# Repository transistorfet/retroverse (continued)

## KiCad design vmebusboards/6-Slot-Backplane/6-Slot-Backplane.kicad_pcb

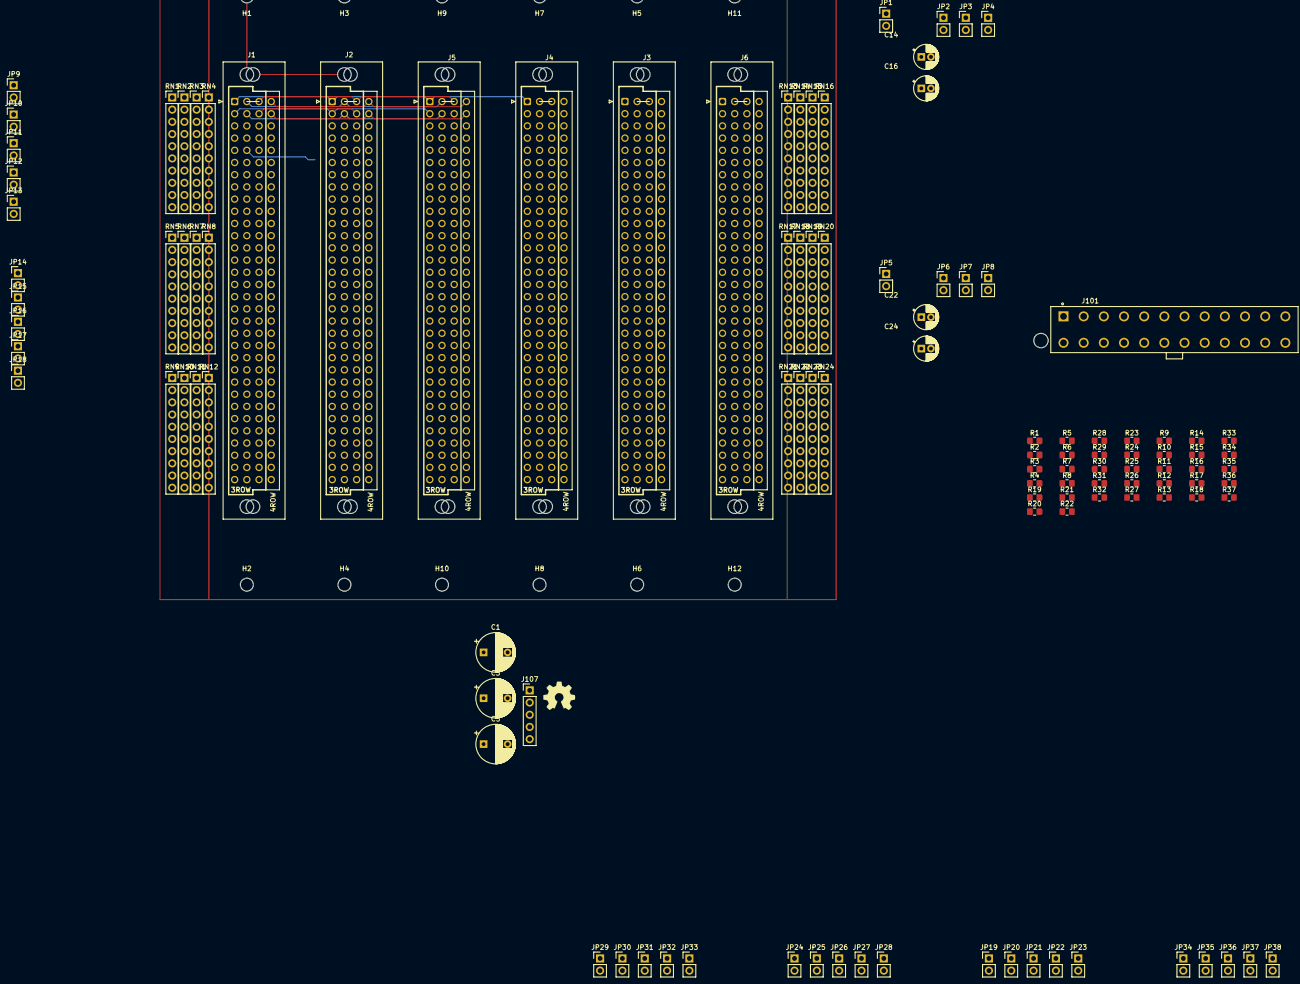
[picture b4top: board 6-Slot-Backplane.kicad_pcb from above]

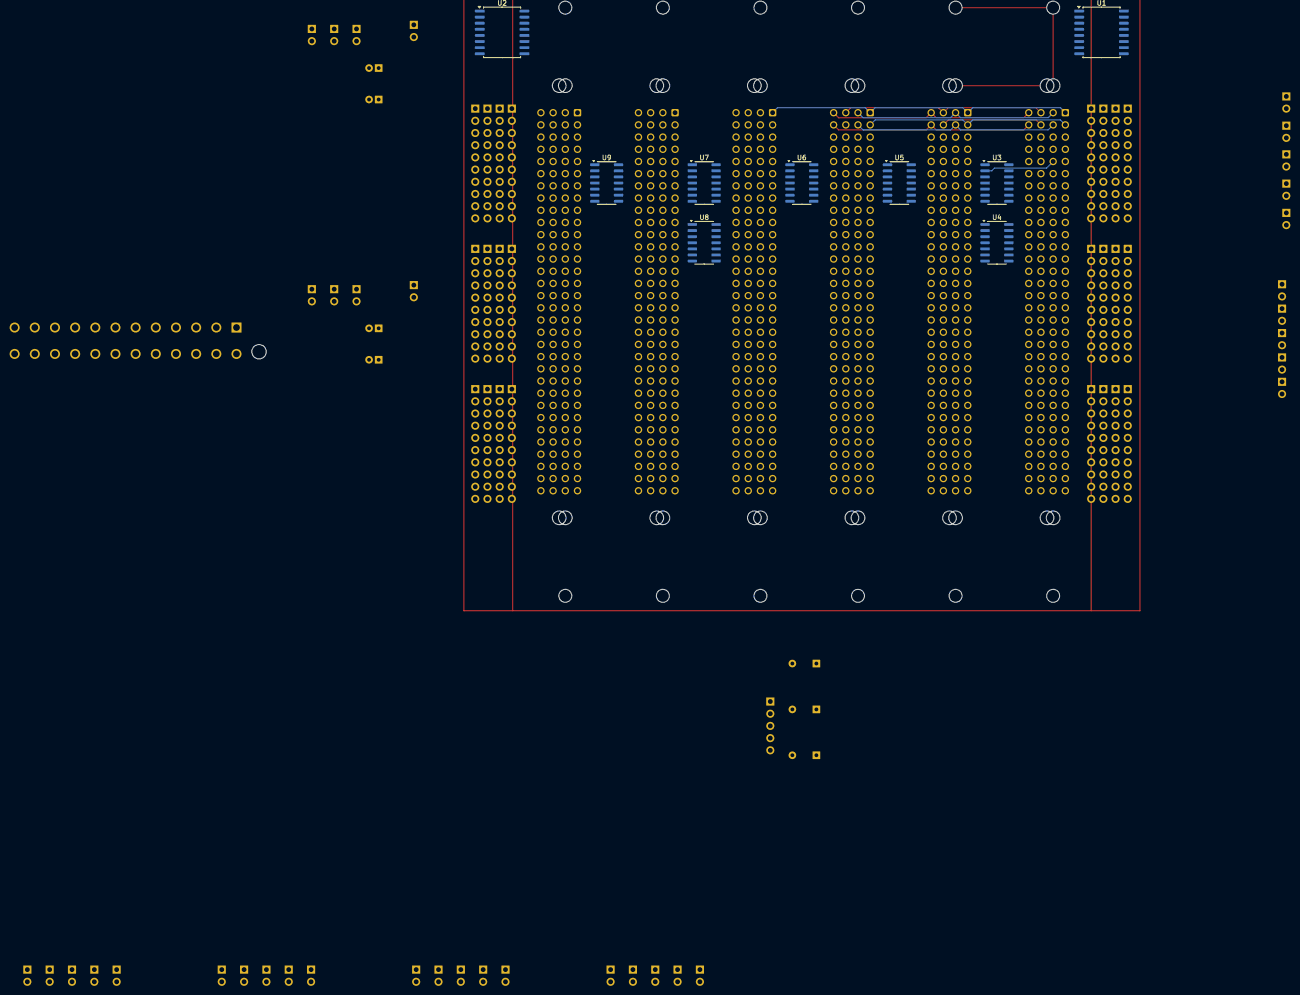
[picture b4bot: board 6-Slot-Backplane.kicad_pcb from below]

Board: 4 copper layers, 136 parts (9 on the bottom side), 139 nets.

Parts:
C1, C3, C5: 10uF; CP_Radial_D8.0mm_P5.00mm
C14, C16, C22, C24: 4.7uF; CP_Radial_D5.0mm_P2.00mm
H1, H2, H3, H4, H5, H6, H7, H8, H9, H10, H11, H12: MountingHole; MountingHole_2.7mm_M2.5_DIN965
J1, J2, J3, J4, J5, J6: VME-J1-4R-NS; DIN41612_C_4x32_Female_Vertical_THT
J101: ATX-24; TE_1-1775099-3_ATX_24_Pin_PowerSupply
J107: SYSTEM MONITOR; PinHeader_1x05_P2.54mm_Vertical
JP1, JP2, JP3, JP4, JP5, JP6, JP7, JP8: PASSIVE/ACTIVE; PinHeader_1x02_P2.54mm_Vertical
JP9: BR0 LOOPBACK; PinHeader_1x02_P2.54mm_Vertical
JP10: BR1 LOOPBACK; PinHeader_1x02_P2.54mm_Vertical
JP11: BR2 LOOPBACK; PinHeader_1x02_P2.54mm_Vertical
JP12: BR3 LOOPBACK; PinHeader_1x02_P2.54mm_Vertical
JP13: IACK LOOPBACK; PinHeader_1x02_P2.54mm_Vertical
JP14, JP19, JP24, JP29, JP34: BG0; PinHeader_1x02_P2.54mm_Vertical
JP15, JP20, JP25, JP30, JP35: BG1; PinHeader_1x02_P2.54mm_Vertical
JP16, JP21, JP26, JP31, JP36: BG2; PinHeader_1x02_P2.54mm_Vertical
JP17, JP22, JP27, JP32, JP37: BG3; PinHeader_1x02_P2.54mm_Vertical
JP18, JP23, JP28, JP33, JP38: IACK; PinHeader_1x02_P2.54mm_Vertical
R1, R4, R6, R8, R20, R22: 470; R_0805_2012Metric_Pad1.20x1.40mm_HandSolder
R2, R3, R5, R7, R19, R21: 330; R_0805_2012Metric_Pad1.20x1.40mm_HandSolder
R9, R10, R11, R12, R13, R14, R15, R16, R17, R18, R23, R24, R25, R26, R27, R28, R29, R30, R31, R32, R33, R34, R35, R36, R37: 82k; R_0805_2012Metric_Pad1.20x1.40mm_HandSolder
RN1, RN2, RN3, RN4, RN5, RN6, RN7, RN8, RN9, RN10, RN11, RN12, RN13, RN14, RN15, RN16, RN17, RN18, RN19, RN20, RN21, RN22, RN23, RN24: 4610X-104-331/471L; PinHeader_1x10_P2.54mm_Vertical
S1: Logo_Open_Hardware_Small; OSHW-Symbol_6.7x6mm_SilkScreen
U1, U2: TCA0372_Dual_OpAmp; SOIC-16W_7.5x10.3mm_P1.27mm
U3, U4, U5, U6, U7, U8, U9: 74ACT32; SOIC-14_3.9x8.7mm_P1.27mm

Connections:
+5V: C1.1, J1.a32 (+5V), J1.b32 (+5V), J1.c32 (+5V), J1.d1 (+5V), J1.d13 (+5V), J1.d32 (+5V), J2.a32 (+5V), J2.b32 (+5V), J2.c32 (+5V), J2.d1 (+5V), J2.d13 (+5V), J2.d32 (+5V), J3.a32 (+5V), J3.b32 (+5V), J3.c32 (+5V), J3.d1 (+5V), J3.d13 (+5V), J3.d32 (+5V), J4.a32 (+5V), J4.b32 (+5V), J4.c32 (+5V), J4.d1 (+5V), J4.d13 (+5V), J4.d32 (+5V), J5.a32 (+5V), J5.b32 (+5V), J5.c32 (+5V), J5.d1 (+5V), J5.d13 (+5V), J5.d32 (+5V), J6.a32 (+5V), J6.b32 (+5V), J6.c32 (+5V), J6.d1 (+5V), J6.d13 (+5V), J6.d32 (+5V), J101.4 (+5V), J101.6 (+5V), J101.21 (+5V), J101.22 (+5V), J101.23 (+5V), J107.4, JP1.1 (A), JP3.1 (A), JP5.1 (A), JP7.1 (A), R3.1, R7.1, R19.1, R21.1, U1.1 (V+), U2.1 (V+), U3.14 (VCC), U4.14 (VCC), U5.14 (VCC), U6.14 (VCC), U7.14 (VCC), U8.14 (VCC), U9.14 (VCC)
+5VStdby: J1.b31 (+5VStdby), J2.b31 (+5VStdby), J3.b31 (+5VStdby), J4.b31 (+5VStdby), J5.b31 (+5VStdby), J6.b31 (+5VStdby), J101.9 (+5VSB)
+12V: C3.1, J1.c31 (+12V), J2.c31 (+12V), J3.c31 (+12V), J4.c31 (+12V), J5.c31 (+12V), J6.c31 (+12V), J101.10 (+12V), J101.11 (+12V)
-12V: C5.1, J1.a31 (-12V), J2.a31 (-12V), J3.a31 (-12V), J4.a31 (-12V), J5.a31 (-12V), J6.a31 (-12V), J101.14 (-12V)
A1: J1.a30 (A01), J2.a30 (A01), J3.a30 (A01), J4.a30 (A01), J5.a30 (A01), J6.a30 (A01), RN3.2 (R1), RN23.2 (R1)
A2: J1.a29 (A02), J2.a29 (A02), J3.a29 (A02), J4.a29 (A02), J5.a29 (A02), J6.a29 (A02), RN3.3 (R2), RN23.3 (R2)
A3: J1.a28 (A03), J2.a28 (A03), J3.a28 (A03), J4.a28 (A03), J5.a28 (A03), J6.a28 (A03), RN3.4 (R3), RN23.4 (R3)
A4: J1.a27 (A04), J2.a27 (A04), J3.a27 (A04), J4.a27 (A04), J5.a27 (A04), J6.a27 (A04), RN3.5 (R4), RN23.5 (R4)
A5: J1.a26 (A05), J2.a26 (A05), J3.a26 (A05), J4.a26 (A05), J5.a26 (A05), J6.a26 (A05), RN3.6 (R5), RN23.6 (R5)
A6: J1.a25 (A06), J2.a25 (A06), J3.a25 (A06), J4.a25 (A06), J5.a25 (A06), J6.a25 (A06), RN3.7 (R6), RN23.7 (R6)
A7: J1.a24 (A07), J2.a24 (A07), J3.a24 (A07), J4.a24 (A07), J5.a24 (A07), J6.a24 (A07), RN3.8 (R7), RN23.8 (R7)
A8: J1.c30 (A8), J2.c30 (A8), J3.c30 (A8), J4.c30 (A8), J5.c30 (A8), J6.c30 (A8), RN4.2 (R1), RN24.2 (R1)
A9: J1.c29 (A9), J2.c29 (A9), J3.c29 (A9), J4.c29 (A9), J5.c29 (A9), J6.c29 (A9), RN4.3 (R2), RN24.3 (R2)
A10: J1.c28 (A10), J2.c28 (A10), J3.c28 (A10), J4.c28 (A10), J5.c28 (A10), J6.c28 (A10), RN4.4 (R3), RN24.4 (R3)
A11: J1.c27 (A11), J2.c27 (A11), J3.c27 (A11), J4.c27 (A11), J5.c27 (A11), J6.c27 (A11), RN4.5 (R4), RN24.5 (R4)
A12: J1.c26 (A12), J2.c26 (A12), J3.c26 (A12), J4.c26 (A12), J5.c26 (A12), J6.c26 (A12), RN4.6 (R5), RN24.6 (R5)
A13: J1.c25 (A13), J2.c25 (A13), J3.c25 (A13), J4.c25 (A13), J5.c25 (A13), J6.c25 (A13), RN4.7 (R6), RN24.7 (R6)
A14: J1.c24 (A14), J2.c24 (A14), J3.c24 (A14), J4.c24 (A14), J5.c24 (A14), J6.c24 (A14), RN4.8 (R7), RN24.8 (R7)
A15: J1.c23 (A15), J2.c23 (A15), J3.c23 (A15), J4.c23 (A15), J5.c23 (A15), J6.c23 (A15), RN4.9 (R8), RN24.9 (R8)
A16: J1.c22 (A16), J2.c22 (A16), J3.c22 (A16), J4.c22 (A16), J5.c22 (A16), J6.c22 (A16), RN5.2 (R1), RN17.2 (R1)
A17: J1.c21 (A17), J2.c21 (A17), J3.c21 (A17), J4.c21 (A17), J5.c21 (A17), J6.c21 (A17), RN5.3 (R2), RN17.3 (R2)
A18: J1.c20 (A18), J2.c20 (A18), J3.c20 (A18), J4.c20 (A18), J5.c20 (A18), J6.c20 (A18), RN5.4 (R3), RN17.4 (R3)
A19: J1.c19 (A19), J2.c19 (A19), J3.c19 (A19), J4.c19 (A19), J5.c19 (A19), J6.c19 (A19), RN5.5 (R4), RN17.5 (R4)
A20: J1.c18 (A20), J2.c18 (A20), J3.c18 (A20), J4.c18 (A20), J5.c18 (A20), J6.c18 (A20), RN5.6 (R5), RN17.6 (R5)
A21: J1.c17 (A21), J2.c17 (A21), J3.c17 (A21), J4.c17 (A21), J5.c17 (A21), J6.c17 (A21), RN5.7 (R6), RN17.7 (R6)
A22: J1.c16 (A22), J2.c16 (A22), J3.c16 (A22), J4.c16 (A22), J5.c16 (A22), J6.c16 (A22), RN5.8 (R7), RN17.8 (R7)
A23: J1.c15 (A23), J2.c15 (A23), J3.c15 (A23), J4.c15 (A23), J5.c15 (A23), J6.c15 (A23), RN5.9 (R8), RN17.9 (R8)
A24: J1.d4 (A24), J2.d4 (A24), J3.d4 (A24), J4.d4 (A24), J5.d4 (A24), J6.d4 (A24), RN6.2 (R1), RN18.2 (R1)
A25: J1.d5 (A25), J2.d5 (A25), J3.d5 (A25), J4.d5 (A25), J5.d5 (A25), J6.d5 (A25), RN6.3 (R2), RN18.3 (R2)
A26: J1.d6 (A26), J2.d6 (A26), J3.d6 (A26), J4.d6 (A26), J5.d6 (A26), J6.d6 (A26), RN6.4 (R3), RN18.4 (R3)
A27: J1.d7 (A27), J2.d7 (A27), J3.d7 (A27), J4.d7 (A27), J5.d7 (A27), J6.d7 (A27), RN6.5 (R4), RN18.5 (R4)
A28: J1.d8 (A28), J2.d8 (A28), J3.d8 (A28), J4.d8 (A28), J5.d8 (A28), J6.d8 (A28), RN6.6 (R5), RN18.6 (R5)
A29: J1.d9 (A29), J2.d9 (A29), J3.d9 (A29), J4.d9 (A29), J5.d9 (A29), J6.d9 (A29), RN6.7 (R6), RN18.7 (R6)
A30: J1.d10 (A30), J2.d10 (A30), J3.d10 (A30), J4.d10 (A30), J5.d10 (A30), J6.d10 (A30), RN6.8 (R7), RN18.8 (R7)
A31: J1.d11 (A31), J2.d11 (A31), J3.d11 (A31), J4.d11 (A31), J5.d11 (A31), J6.d11 (A31), RN6.9 (R8), RN18.9 (R8)
AM0: J1.b16 (AM0), J2.b16 (AM0), J3.b16 (AM0), J4.b16 (AM0), J5.b16 (AM0), J6.b16 (AM0), RN10.9 (R8), RN14.9 (R8)
AM1: J1.b17 (AM1), J2.b17 (AM1), J3.b17 (AM1), J4.b17 (AM1), J5.b17 (AM1), J6.b17 (AM1), RN11.2 (R1), RN15.2 (R1)
AM2: J1.b18 (AM2), J2.b18 (AM2), J3.b18 (AM2), J4.b18 (AM2), J5.b18 (AM2), J6.b18 (AM2), RN11.3 (R2), RN15.3 (R2)
AM3: J1.b19 (AM3), J2.b19 (AM3), J3.b19 (AM3), J4.b19 (AM3), J5.b19 (AM3), J6.b19 (AM3), RN11.4 (R3), RN15.4 (R3)
AM4: J1.a23 (AM4), J2.a23 (AM4), J3.a23 (AM4), J4.a23 (AM4), J5.a23 (AM4), J6.a23 (AM4), RN9.9 (R8), RN13.9 (R8)
AM5: J1.c14 (AM5), J2.c14 (AM5), J3.c14 (AM5), J4.c14 (AM5), J5.c14 (AM5), J6.c14 (AM5), RN3.9 (R8), RN23.9 (R8)
D0: J1.a1 (D00), J2.a1 (D00), J3.a1 (D00), J4.a1 (D00), J5.a1 (D00), J6.a1 (D00), RN1.2 (R1), RN21.2 (R1)
D1: J1.a2 (D01), J2.a2 (D01), J3.a2 (D01), J4.a2 (D01), J5.a2 (D01), J6.a2 (D01), RN1.3 (R2), RN21.3 (R2)
D2: J1.a3 (D02), J2.a3 (D02), J3.a3 (D02), J4.a3 (D02), J5.a3 (D02), J6.a3 (D02), RN1.4 (R3), RN21.4 (R3)
D3: J1.a4 (D03), J2.a4 (D03), J3.a4 (D03), J4.a4 (D03), J5.a4 (D03), J6.a4 (D03), RN1.5 (R4), RN21.5 (R4)
D4: J1.a5 (D04), J2.a5 (D04), J3.a5 (D04), J4.a5 (D04), J5.a5 (D04), J6.a5 (D04), RN1.6 (R5), RN21.6 (R5)
D5: J1.a6 (D05), J2.a6 (D05), J3.a6 (D05), J4.a6 (D05), J5.a6 (D05), J6.a6 (D05), RN1.7 (R6), RN21.7 (R6)
D6: J1.a7 (D06), J2.a7 (D06), J3.a7 (D06), J4.a7 (D06), J5.a7 (D06), J6.a7 (D06), RN1.8 (R7), RN21.8 (R7)
D7: J1.a8 (D07), J2.a8 (D07), J3.a8 (D07), J4.a8 (D07), J5.a8 (D07), J6.a8 (D07), RN1.9 (R8), RN21.9 (R8)
D8: J1.c1 (D08), J2.c1 (D08), J3.c1 (D08), J4.c1 (D08), J5.c1 (D08), J6.c1 (D08), RN2.2 (R1), RN22.2 (R1)
D9: J1.c2 (D09), J2.c2 (D09), J3.c2 (D09), J4.c2 (D09), J5.c2 (D09), J6.c2 (D09), RN2.3 (R2), RN22.3 (R2)
D10: J1.c3 (D10), J2.c3 (D10), J3.c3 (D10), J4.c3 (D10), J5.c3 (D10), J6.c3 (D10), RN2.4 (R3), RN22.4 (R3)
D11: J1.c4 (D11), J2.c4 (D11), J3.c4 (D11), J4.c4 (D11), J5.c4 (D11), J6.c4 (D11), RN2.5 (R4), RN22.5 (R4)
D12: J1.c5 (D12), J2.c5 (D12), J3.c5 (D12), J4.c5 (D12), J5.c5 (D12), J6.c5 (D12), RN2.6 (R5), RN22.6 (R5)
D13: J1.c6 (D13), J2.c6 (D13), J3.c6 (D13), J4.c6 (D13), J5.c6 (D13), J6.c6 (D13), RN2.7 (R6), RN22.7 (R6)
D14: J1.c7 (D14), J2.c7 (D14), J3.c7 (D14), J4.c7 (D14), J5.c7 (D14), J6.c7 (D14), RN2.8 (R7), RN22.8 (R7)
D15: J1.c8 (D15), J2.c8 (D15), J3.c8 (D15), J4.c8 (D15), J5.c8 (D15), J6.c8 (D15), RN2.9 (R8), RN22.9 (R8)
D16: J1.d14 (D16), J2.d14 (D16), J3.d14 (D16), J4.d14 (D16), J5.d14 (D16), J6.d14 (D16), RN7.2 (R1), RN19.2 (R1)
D17: J1.d15 (D17), J2.d15 (D17), J3.d15 (D17), J4.d15 (D17), J5.d15 (D17), J6.d15 (D17), RN7.3 (R2), RN19.3 (R2)
D18: J1.d16 (D18), J2.d16 (D18), J3.d16 (D18), J4.d16 (D18), J5.d16 (D18), J6.d16 (D18), RN7.4 (R3), RN19.4 (R3)
D19: J1.d17 (D19), J2.d17 (D19), J3.d17 (D19), J4.d17 (D19), J5.d17 (D19), J6.d17 (D19), RN7.5 (R4), RN19.5 (R4)
D20: J1.d18 (D20), J2.d18 (D20), J3.d18 (D20), J4.d18 (D20), J5.d18 (D20), J6.d18 (D20), RN7.6 (R5), RN19.6 (R5)
D21: J1.d19 (D21), J2.d19 (D21), J3.d19 (D21), J4.d19 (D21), J5.d19 (D21), J6.d19 (D21), RN7.7 (R6), RN19.7 (R6)
D22: J1.d20 (D22), J2.d20 (D22), J3.d20 (D22), J4.d20 (D22), J5.d20 (D22), J6.d20 (D22), RN7.8 (R7), RN19.8 (R7)
D23: J1.d21 (D23), J2.d21 (D23), J3.d21 (D23), J4.d21 (D23), J5.d21 (D23), J6.d21 (D23), RN7.9 (R8), RN19.9 (R8)
D24: J1.d23 (D24), J2.d23 (D24), J3.d23 (D24), J4.d23 (D24), J5.d23 (D24), J6.d23 (D24), RN8.2 (R1), RN20.2 (R1)
D25: J1.d24 (D25), J2.d24 (D25), J3.d24 (D25), J4.d24 (D25), J5.d24 (D25), J6.d24 (D25), RN8.3 (R2), RN20.3 (R2)
D26: J1.d25 (D26), J2.d25 (D26), J3.d25 (D26), J4.d25 (D26), J5.d25 (D26), J6.d25 (D26), RN8.4 (R3), RN20.4 (R3)
D27: J1.d26 (D27), J2.d26 (D27), J3.d26 (D27), J4.d26 (D27), J5.d26 (D27), J6.d26 (D27), RN8.5 (R4), RN20.5 (R4)
D28: J1.d27 (D28), J2.d27 (D28), J3.d27 (D28), J4.d27 (D28), J5.d27 (D28), J6.d27 (D28), RN8.6 (R5), RN20.6 (R5)
D29: J1.d28 (D29), J2.d28 (D29), J3.d28 (D29), J4.d28 (D29), J5.d28 (D29), J6.d28 (D29), RN8.7 (R6), RN20.7 (R6)
D30: J1.d29 (D30), J2.d29 (D30), J3.d29 (D30), J4.d29 (D30), J5.d29 (D30), J6.d29 (D30), RN8.8 (R7), RN20.8 (R7)
D31: J1.d30 (D31), J2.d30 (D31), J3.d30 (D31), J4.d30 (D31), J5.d30 (D31), J6.d30 (D31), RN8.9 (R8), RN20.9 (R8)
GND: C1.2, C3.2, C5.2, C14.2, C16.2, C22.2, C24.2, J1.a9 (GND), J1.a11 (GND), J1.a15 (GND), J1.a17 (GND), J1.a19 (GND), J1.b20 (GND), J1.b23 (GND), J1.c9 (GND), J1.d2 (GND), J1.d12 (GND), J1.d22 (GND), J1.d31 (GND), J2.a9 (GND), J2.a11 (GND), J2.a15 (GND), J2.a17 (GND), J2.a19 (GND), J2.b20 (GND), J2.b23 (GND), J2.c9 (GND), J2.d2 (GND), J2.d12 (GND), J2.d22 (GND), J2.d31 (GND), J3.a9 (GND), J3.a11 (GND), J3.a15 (GND), J3.a17 (GND), J3.a19 (GND), J3.b20 (GND), J3.b23 (GND), J3.c9 (GND), J3.d2 (GND), J3.d12 (GND), J3.d22 (GND), J3.d31 (GND), J4.a9 (GND), J4.a11 (GND), J4.a15 (GND), J4.a17 (GND), J4.a19 (GND), J4.b20 (GND), J4.b23 (GND), J4.c9 (GND), J4.d2 (GND), J4.d12 (GND), J4.d22 (GND), J4.d31 (GND), J5.a9 (GND), J5.a11 (GND), J5.a15 (GND), J5.a17 (GND), J5.a19 (GND), J5.b20 (GND), J5.b23 (GND), J5.c9 (GND), J5.d2 (GND), J5.d12 (GND), J5.d22 (GND), J5.d31 (GND), J6.a9 (GND), J6.a11 (GND), J6.a15 (GND), J6.a17 (GND), J6.a19 (GND), J6.b20 (GND), J6.b23 (GND), J6.c9 (GND), J6.d2 (GND), J6.d12 (GND), J6.d22 (GND), J6.d31 (GND), J101.3 (GND), J101.5 (GND), J101.7 (GND), J101.15 (GND), J101.16 (PS_ON#), J101.17 (GND), J101.18 (GND), J101.19 (GND), J101.24 (GND), J107.5, JP2.1 (A), JP4.1 (A), JP6.1 (A), JP8.1 (A), R4.2, R8.2, R9.2, R10.2, R11.2, R12.2, R13.2, R14.2, R15.2, R16.2, R17.2, R18.2, R20.2, R22.2, R23.2, R24.2, R25.2, R26.2, R27.2, R28.2, R29.2, R30.2, R31.2, R32.2, R33.2, R34.2, R35.2, R36.2, R37.2, U1.4 (V-), U1.5 (V-), U1.12 (V-), U1.13 (V-), U2.4 (V-), U2.5 (V-), U2.12 (V-), U2.13 (V-), U3.7 (GND), U4.7 (GND), U5.7 (GND), U6.7 (GND), U7.7 (GND), U8.7 (GND), U9.7 (GND)
unnamed: J101.1 (+3.3V), J101.2 (+3.3V), J101.12 (+3.3V), J101.13 (+3.3V)
unnamed: C14.1, U1.9 (+), U1.16
unnamed: C16.1, U1.2, U1.8 (+)
unnamed: C22.1, U2.9 (+), U2.16
unnamed: C24.1, U2.2, U2.8 (+)
unnamed: R3.2, R4.1, U1.10 (-)
unnamed: R19.2, R20.1, U1.7 (-)
unnamed: R7.2, R8.1, U2.10 (-)
unnamed: R21.2, R22.1, U2.7 (-)
SYSCLK: J1.a10 (SYSCLK), J2.a10 (SYSCLK), J3.a10 (SYSCLK), J4.a10 (SYSCLK), J5.a10 (SYSCLK), J6.a10 (SYSCLK), RN9.2 (R1), RN13.2 (R1)
TERM_L1_HIGH: JP1.2 (C), RN1.10 (COM2), RN2.10 (COM2), RN3.10 (COM2), RN4.10 (COM2), RN5.10 (COM2), RN9.10 (COM2), RN10.10 (COM2), RN11.10 (COM2), RN12.10 (COM2)
TERM_L1_LOW: JP2.2 (C), RN1.1 (COM1), RN2.1 (COM1), RN3.1 (COM1), RN4.1 (COM1), RN5.1 (COM1), RN9.1 (COM1), RN10.1 (COM1), RN11.1 (COM1), RN12.1 (COM1)
TERM_L2_HIGH: JP3.2 (C), R2.2, RN6.10 (COM2), RN7.10 (COM2), RN8.10 (COM2)
TERM_L2_LOW: JP4.2 (C), R1.1, RN6.1 (COM1), RN7.1 (COM1), RN8.1 (COM1)
TERM_R1_HIGH: JP5.2 (C), RN13.10 (COM2), RN14.10 (COM2), RN15.10 (COM2), RN16.10 (COM2), RN17.10 (COM2), RN21.10 (COM2), RN22.10 (COM2), RN23.10 (COM2), RN24.10 (COM2)
TERM_R1_LOW: JP6.2 (C), RN13.1 (COM1), RN14.1 (COM1), RN15.1 (COM1), RN16.1 (COM1), RN17.1 (COM1), RN21.1 (COM1), RN22.1 (COM1), RN23.1 (COM1), RN24.1 (COM1)
TERM_R2_HIGH: JP7.2 (C), R5.2, RN18.10 (COM2), RN19.10 (COM2), RN20.10 (COM2)
TERM_R2_LOW: JP8.2 (C), R6.1, RN18.1 (COM1), RN19.1 (COM1), RN20.1 (COM1)
~ACFAIL: J1.b3 (~ACFAIL), J2.b3 (~ACFAIL), J3.b3 (~ACFAIL), J4.b3 (~ACFAIL), J5.b3 (~ACFAIL), J6.b3 (~ACFAIL), J107.3, RN10.4 (R3), RN14.4 (R3)
~AS: J1.a18 (~AS), J2.a18 (~AS), J3.a18 (~AS), J4.a18 (~AS), J5.a18 (~AS), J6.a18 (~AS), RN9.7 (R6), RN13.7 (R6)
~BBSY: J1.b1 (~BBSY), J2.b1 (~BBSY), J3.b1 (~BBSY), J4.b1 (~BBSY), J5.b1 (~BBSY), J6.b1 (~BBSY), RN10.2 (R1), RN14.2 (R1)
~BCLR: J1.b2 (~BCLR), J2.b2 (~BCLR), J3.b2 (~BCLR), J4.b2 (~BCLR), J5.b2 (~BCLR), J6.b2 (~BCLR), RN10.3 (R2), RN14.3 (R2)
~BERR: J1.c11 (~BERR), J2.c11 (~BERR), J3.c11 (~BERR), J4.c11 (~BERR), J5.c11 (~BERR), J6.c11 (~BERR), RN12.7 (R6), RN16.7 (R6)
~BR0: J1.b12 (~BR0), J2.b12 (~BR0), J3.b12 (~BR0), J4.b12 (~BR0), J5.b12 (~BR0), J6.b12 (~BR0), JP9.1 (A), RN10.5 (R4), RN14.5 (R4)
~BR1: J1.b13 (~BR1), J2.b13 (~BR1), J3.b13 (~BR1), J4.b13 (~BR1), J5.b13 (~BR1), J6.b13 (~BR1), JP10.1 (A), RN10.6 (R5), RN14.6 (R5)
~BR2: J1.b14 (~BR2), J2.b14 (~BR2), J3.b14 (~BR2), J4.b14 (~BR2), J5.b14 (~BR2), J6.b14 (~BR2), JP11.1 (A), RN10.7 (R6), RN14.7 (R6)
~BR3: J1.b15 (~BR3), J2.b15 (~BR3), J3.b15 (~BR3), J4.b15 (~BR3), J5.b15 (~BR3), J6.b15 (~BR3), JP12.1 (A), RN10.8 (R7), RN14.8 (R7)
~DS0: J1.a13 (~DS0), J2.a13 (~DS0), J3.a13 (~DS0), J4.a13 (~DS0), J5.a13 (~DS0), J6.a13 (~DS0), RN9.4 (R3), RN13.4 (R3)
~DS1: J1.a12 (~DS1), J2.a12 (~DS1), J3.a12 (~DS1), J4.a12 (~DS1), J5.a12 (~DS1), J6.a12 (~DS1), RN9.3 (R2), RN13.3 (R2)
~DTACK: J1.a16 (~DTACK), J2.a16 (~DTACK), J3.a16 (~DTACK), J4.a16 (~DTACK), J5.a16 (~DTACK), J6.a16 (~DTACK), RN9.6 (R5), RN13.6 (R5)
~IACK: J1.a20 (~IACK), J2.a20 (~IACK), J3.a20 (~IACK), J4.a20 (~IACK), J5.a20 (~IACK), J6.a20 (~IACK), JP13.1 (A), RN9.8 (R7), RN13.8 (R7)
~IRQ1: J1.b30 (~IRQ1), J2.b30 (~IRQ1), J3.b30 (~IRQ1), J4.b30 (~IRQ1), J5.b30 (~IRQ1), J6.b30 (~IRQ1), RN12.5 (R4), RN16.5 (R4)
~IRQ2: J1.b29 (~IRQ2), J2.b29 (~IRQ2), J3.b29 (~IRQ2), J4.b29 (~IRQ2), J5.b29 (~IRQ2), J6.b29 (~IRQ2), RN12.4 (R3), RN16.4 (R3)
~IRQ3: J1.b28 (~IRQ3), J2.b28 (~IRQ3), J3.b28 (~IRQ3), J4.b28 (~IRQ3), J5.b28 (~IRQ3), J6.b28 (~IRQ3), RN12.3 (R2), RN16.3 (R2)
~IRQ4: J1.b27 (~IRQ4), J2.b27 (~IRQ4), J3.b27 (~IRQ4), J4.b27 (~IRQ4), J5.b27 (~IRQ4), J6.b27 (~IRQ4), RN12.2 (R1), RN16.2 (R1)
~IRQ5: J1.b26 (~IRQ5), J2.b26 (~IRQ5), J3.b26 (~IRQ5), J4.b26 (~IRQ5), J5.b26 (~IRQ5), J6.b26 (~IRQ5), RN11.9 (R8), RN15.9 (R8)
~IRQ6: J1.b25 (~IRQ6), J2.b25 (~IRQ6), J3.b25 (~IRQ6), J4.b25 (~IRQ6), J5.b25 (~IRQ6), J6.b25 (~IRQ6), RN11.8 (R7), RN15.8 (R7)
~IRQ7: J1.b24 (~IRQ7), J2.b24 (~IRQ7), J3.b24 (~IRQ7), J4.b24 (~IRQ7), J5.b24 (~IRQ7), J6.b24 (~IRQ7), RN11.7 (R6), RN15.7 (R6)
~LWORD: J1.c13 (~LWORD), J2.c13 (~LWORD), J3.c13 (~LWORD), J4.c13 (~LWORD), J5.c13 (~LWORD), J6.c13 (~LWORD), RN12.9 (R8), RN16.9 (R8)
~RETRY: J1.d3 (~RETRY), J2.d3 (~RETRY), J3.d3 (~RETRY), J4.d3 (~RETRY), J5.d3 (~RETRY), J6.d3 (~RETRY), R1.2, R2.1, R5.1, R6.2
~SERCLK: J1.b21 (SERCLK), J2.b21 (SERCLK), J3.b21 (SERCLK), J4.b21 (SERCLK), J5.b21 (SERCLK), J6.b21 (SERCLK), RN11.5 (R4), RN15.5 (R4)
~SERDAT: J1.b22 (SERDAT), J2.b22 (SERDAT), J3.b22 (SERDAT), J4.b22 (SERDAT), J5.b22 (SERDAT), J6.b22 (SERDAT), RN11.6 (R5), RN15.6 (R5)
~SLOT1_BG0IN: J1.b4 (~BG0IN), JP9.2 (B), JP14.2 (B), JP19.2 (B), JP24.2 (B), JP29.2 (B), JP34.2 (B), U3.1, U4.4, U5.9, U6.12, U8.1
~SLOT1_BG0OUT: J1.b5 (~BG0OUT), JP14.1 (A), JP19.1 (A), JP24.1 (A), JP29.1 (A), JP34.1 (A), R9.1, R14.1, R23.1, R28.1, R33.1, U3.2, U4.5, U5.10, U6.13, U8.2
~SLOT1_BG1IN: J1.b6 (~BG1IN), JP10.2 (B), JP15.2 (B), JP20.2 (B), JP25.2 (B), JP30.2 (B), JP35.2 (B), U3.4, U4.9, U5.12, U7.1, U8.4
~SLOT1_BG1OUT: J1.b7 (~BG1OUT), JP15.1 (A), JP20.1 (A), JP25.1 (A), JP30.1 (A), JP35.1 (A), R10.1, R15.1, R24.1, R29.1, R34.1, U3.5, U4.10, U5.13, U7.2, U8.5
~SLOT1_BG2IN: J1.b8 (~BG2IN), JP11.2 (B), JP16.2 (B), JP21.2 (B), JP26.2 (B), JP31.2 (B), JP36.2 (B), U3.9, U4.12, U6.1, U7.4, U8.9
~SLOT1_BG2OUT: J1.b9 (~BG2OUT), JP16.1 (A), JP21.1 (A), JP26.1 (A), JP31.1 (A), JP36.1 (A), R11.1, R16.1, R25.1, R30.1, R35.1, U3.10, U4.13, U6.2, U7.5, U8.10
~SLOT1_BG3IN: J1.b10 (~BG3IN), JP12.2 (B), JP17.2 (B), JP22.2 (B), JP27.2 (B), JP32.2 (B), JP37.2 (B), U3.12, U5.1, U6.4, U7.9, U8.12
~SLOT1_BG3OUT: J1.b11 (~BG3OUT), JP17.1 (A), JP22.1 (A), JP27.1 (A), JP32.1 (A), JP37.1 (A), R12.1, R17.1, R26.1, R31.1, R36.1, U3.13, U5.2, U6.5, U7.10, U8.13
~SLOT1_IACKIN: J1.a21 (~IACKIN), JP13.2 (B), JP18.2 (B), JP23.2 (B), JP28.2 (B), JP33.2 (B), JP38.2 (B), U4.1, U5.4, U6.9, U7.12, U9.1
~SLOT1_IACKOUT: J1.a22 (~IACKOUT), JP18.1 (A), JP23.1 (A), JP28.1 (A), JP33.1 (A), JP38.1 (A), R13.1, R18.1, R27.1, R32.1, R37.1, U4.2, U5.5, U6.10, U7.13, U9.2
~SLOT2_BG0IN: J2.b4 (~BG0IN), J3.b4 (~BG0IN), J4.b4 (~BG0IN), J5.b4 (~BG0IN), J6.b4 (~BG0IN), U3.3, U4.6, U5.8, U6.11, U8.3
~SLOT2_BG0OUT: J2.b5 (~BG0OUT), J3.b5 (~BG0OUT), J4.b5 (~BG0OUT), J5.b5 (~BG0OUT), J6.b5 (~BG0OUT)
~SLOT2_BG1IN: J2.b6 (~BG1IN), J3.b6 (~BG1IN), J4.b6 (~BG1IN), J5.b6 (~BG1IN), J6.b6 (~BG1IN), U3.6, U4.8, U5.11, U7.3, U8.6
~SLOT2_BG1OUT: J2.b7 (~BG1OUT), J3.b7 (~BG1OUT), J4.b7 (~BG1OUT), J5.b7 (~BG1OUT), J6.b7 (~BG1OUT)
~SLOT2_BG2IN: J2.b8 (~BG2IN), J3.b8 (~BG2IN), J4.b8 (~BG2IN), J5.b8 (~BG2IN), J6.b8 (~BG2IN), U3.8, U4.11, U6.3, U7.6, U8.8
~SLOT2_BG2OUT: J2.b9 (~BG2OUT), J3.b9 (~BG2OUT), J4.b9 (~BG2OUT), J5.b9 (~BG2OUT), J6.b9 (~BG2OUT)
~SLOT2_BG3IN: J2.b10 (~BG3IN), J3.b10 (~BG3IN), J4.b10 (~BG3IN), J5.b10 (~BG3IN), J6.b10 (~BG3IN), U3.11, U5.3, U6.6, U7.8, U8.11
~SLOT2_BG3OUT: J2.b11 (~BG3OUT), J3.b11 (~BG3OUT), J4.b11 (~BG3OUT), J5.b11 (~BG3OUT), J6.b11 (~BG3OUT)
~SLOT2_IACKIN: J2.a21 (~IACKIN), J3.a21 (~IACKIN), J4.a21 (~IACKIN), J5.a21 (~IACKIN), J6.a21 (~IACKIN), U4.3, U5.6, U6.8, U7.11, U9.3
~SLOT2_IACKOUT: J2.a22 (~IACKOUT), J3.a22 (~IACKOUT), J4.a22 (~IACKOUT), J5.a22 (~IACKOUT), J6.a22 (~IACKOUT)
~SYSFAIL: J1.c10 (~SYSFAIL), J2.c10 (~SYSFAIL), J3.c10 (~SYSFAIL), J4.c10 (~SYSFAIL), J5.c10 (~SYSFAIL), J6.c10 (~SYSFAIL), J107.2, RN12.6 (R5), RN16.6 (R5)
~SYSRESET: J1.c12 (~SYSRESET), J2.c12 (~SYSRESET), J3.c12 (~SYSRESET), J4.c12 (~SYSRESET), J5.c12 (~SYSRESET), J6.c12 (~SYSRESET), J107.1, RN12.8 (R7), RN16.8 (R7)
~WRITE: J1.a14 (~WRITE), J2.a14 (~WRITE), J3.a14 (~WRITE), J4.a14 (~WRITE), J5.a14 (~WRITE), J6.a14 (~WRITE), RN9.5 (R4), RN13.5 (R4)

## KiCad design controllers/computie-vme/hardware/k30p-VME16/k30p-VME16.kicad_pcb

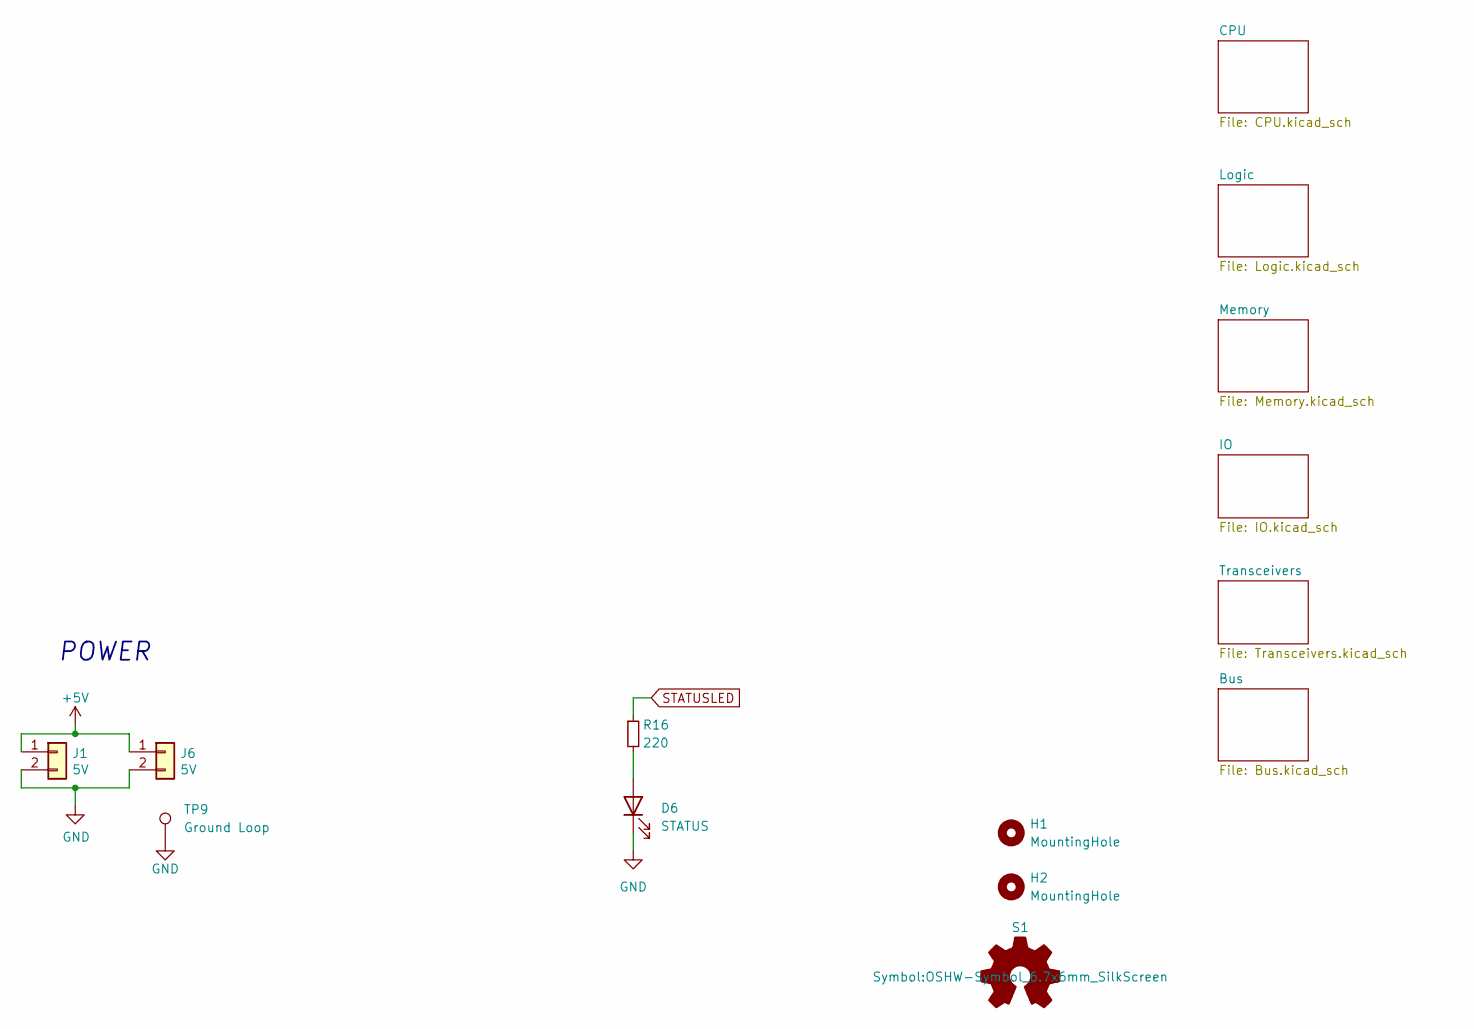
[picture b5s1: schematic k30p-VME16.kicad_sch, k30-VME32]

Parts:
D6: STATUS; LED_D3.0mm
H1, H2: MountingHole; MountingHole_2.7mm_M2.5_DIN965
J1, J6: 5V; PinHeader_1x02_P2.54mm_Vertical
R16: 220; R_Axial_DIN0204_L3.6mm_D1.6mm_P5.08mm_Horizontal
S1: Logo_Open_Hardware_Small; OSHW-Symbol_6.7x6mm_SilkScreen
TP9: Ground Loop; TestPoint_Loop_D2.60mm_Drill1.6mm_Beaded

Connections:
+5V: J1.1, J6.1; also elsewhere on the board
GND: D6.1 (K), J1.2, J6.2, TP9.1; also elsewhere on the board
unnamed: D6.2 (A), R16.2
STATUSLED: R16.1

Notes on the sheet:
POWER

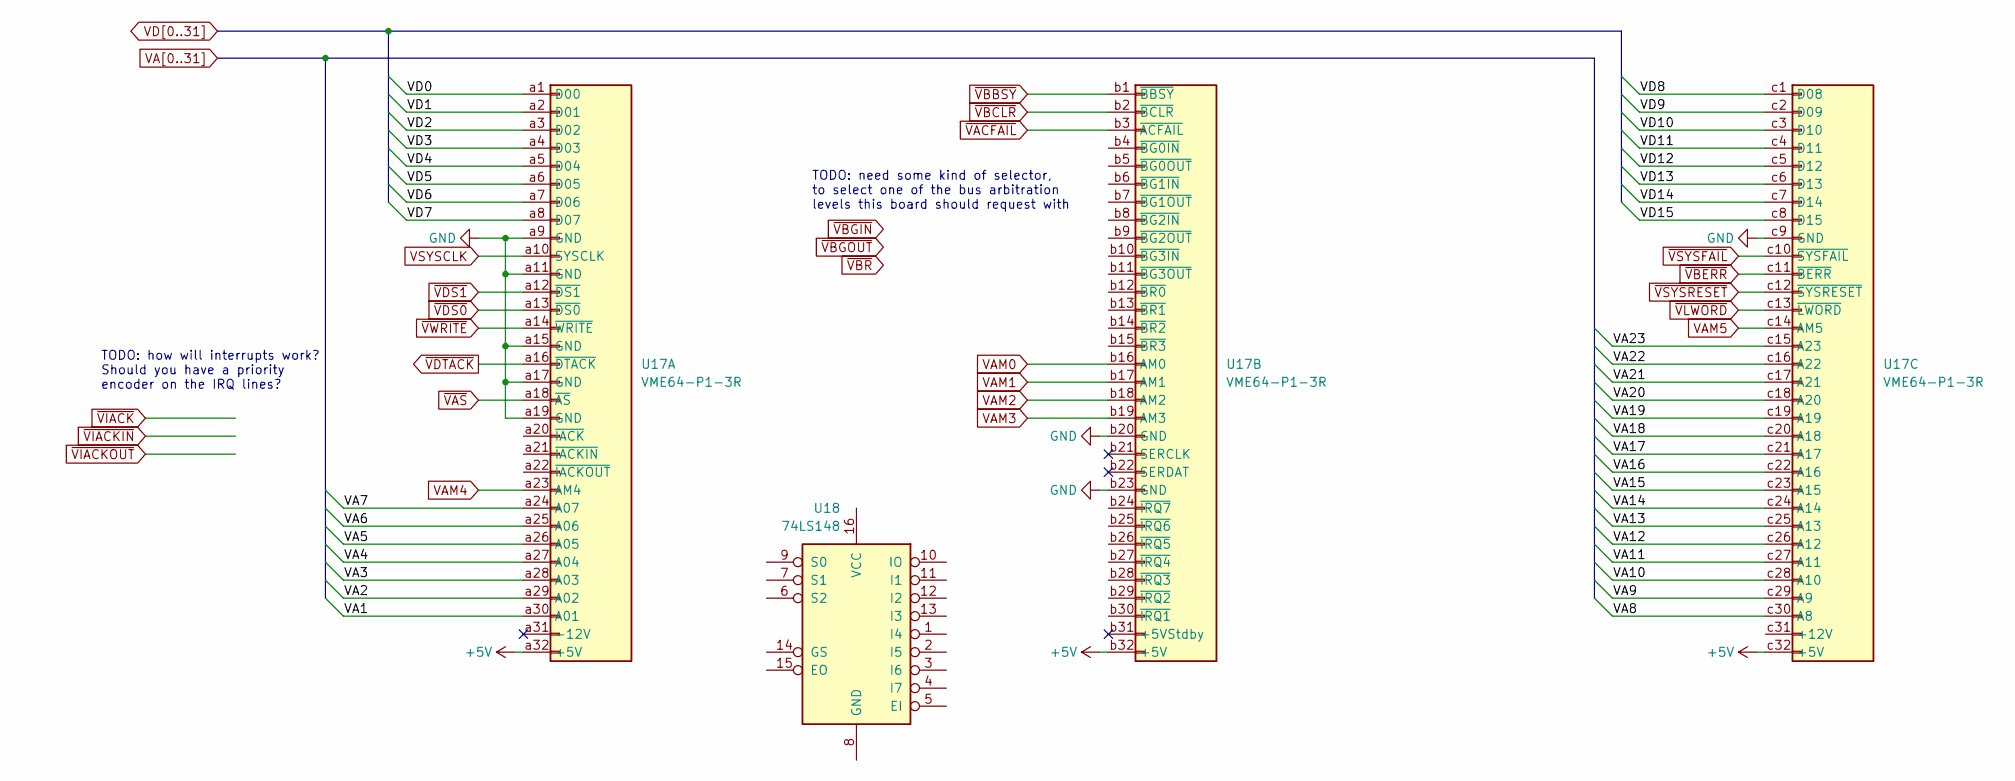
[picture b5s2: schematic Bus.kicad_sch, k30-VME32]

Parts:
U17: VME64-P1-3R
U18: 74LS148

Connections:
+5V: U17.a32 (+5V), U17.b32 (+5V), U17.c32 (+5V); also elsewhere on the board
+12V: U17.c31 (+12V)
GND: U17.a9 (GND), U17.a11 (GND), U17.a15 (GND), U17.a17 (GND), U17.a19 (GND), U17.b20 (GND), U17.b23 (GND), U17.c9 (GND); also elsewhere on the board
VA1: U17.a30 (A01); also elsewhere on the board
VA2: U17.a29 (A02); also elsewhere on the board
VA3: U17.a28 (A03); also elsewhere on the board
VA4: U17.a27 (A04); also elsewhere on the board
VA5: U17.a26 (A05); also elsewhere on the board
VA6: U17.a25 (A06); also elsewhere on the board
VA7: U17.a24 (A07); also elsewhere on the board
VA8: U17.c30 (A8); also elsewhere on the board
VA9: U17.c29 (A9); also elsewhere on the board
VA10: U17.c28 (A10); also elsewhere on the board
VA11: U17.c27 (A11); also elsewhere on the board
VA12: U17.c26 (A12); also elsewhere on the board
VA13: U17.c25 (A13); also elsewhere on the board
VA14: U17.c24 (A14); also elsewhere on the board
VA15: U17.c23 (A15); also elsewhere on the board
VA16: U17.c22 (A16); also elsewhere on the board
VA17: U17.c21 (A17); also elsewhere on the board
VA18: U17.c20 (A18); also elsewhere on the board
VA19: U17.c19 (A19); also elsewhere on the board
VA20: U17.c18 (A20); also elsewhere on the board
VA21: U17.c17 (A21); also elsewhere on the board
VA22: U17.c16 (A22); also elsewhere on the board
VA23: U17.c15 (A23); also elsewhere on the board
VAM0: U17.b16 (AM0)
VAM1: U17.b17 (AM1)
VAM2: U17.b18 (AM2)
VAM3: U17.b19 (AM3)
VAM4: U17.a23 (AM4)
VAM5: U17.c14 (AM5)
VD0: U17.a1 (D00); also elsewhere on the board
VD1: U17.a2 (D01); also elsewhere on the board
VD2: U17.a3 (D02); also elsewhere on the board
VD3: U17.a4 (D03); also elsewhere on the board
VD4: U17.a5 (D04); also elsewhere on the board
VD5: U17.a6 (D05); also elsewhere on the board
VD6: U17.a7 (D06); also elsewhere on the board
VD7: U17.a8 (D07); also elsewhere on the board
VD8: U17.c1 (D08); also elsewhere on the board
VD9: U17.c2 (D09); also elsewhere on the board
VD10: U17.c3 (D10); also elsewhere on the board
VD11: U17.c4 (D11); also elsewhere on the board
VD12: U17.c5 (D12); also elsewhere on the board
VD13: U17.c6 (D13); also elsewhere on the board
VD14: U17.c7 (D14); also elsewhere on the board
VD15: U17.c8 (D15); also elsewhere on the board
VSYSCLK: U17.a10 (SYSCLK)
~VACFAIL: U17.b3 (~ACFAIL)
~VAS: U17.a18 (~AS)
~VBBSY: U17.b1 (~BBSY)
~VBCLR: U17.b2 (~BCLR)
~VBERR: U17.c11 (~BERR)
~VDS0: U17.a13 (~DS0)
~VDS1: U17.a12 (~DS1)
~VDTACK: U17.a16 (~DTACK)
~VLWORD: U17.c13 (~LWORD)
~VSYSFAIL: U17.c10 (~SYSFAIL)
~VSYSRESET: U17.c12 (~SYSRESET)
~VWRITE: U17.a14 (~WRITE)

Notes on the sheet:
TODO: need some kind of selector, to select one of the bus arbitration levels this board should request with
TODO: how will interrupts work? Should you have a priority encoder on the IRQ lines?

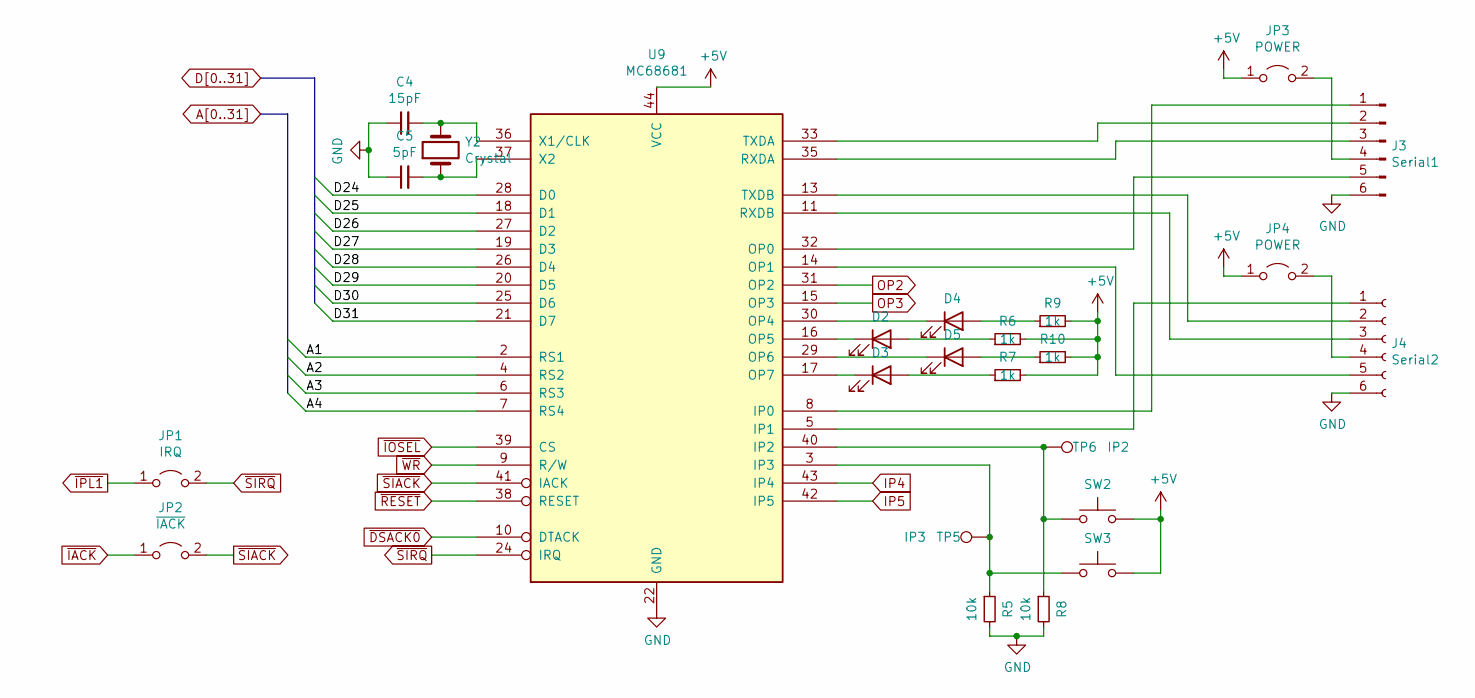
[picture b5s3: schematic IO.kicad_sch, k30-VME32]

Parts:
C4: 15pF; C_Disc_D3.0mm_W2.0mm_P2.50mm
C5: 5pF; C_Disc_D3.0mm_W2.0mm_P2.50mm
D2: OP5; LED_D5.0mm
D3: OP7; LED_D5.0mm
D4: OP4; LED_D5.0mm
D5: OP6; LED_D5.0mm
J3: Serial1; PinHeader_1x06_P2.54mm_Vertical
J4: Serial2; PinHeader_1x06_P2.54mm_Vertical
JP1: IRQ; PinHeader_1x02_P2.54mm_Vertical
JP2: ~{IACK}; PinHeader_1x02_P2.54mm_Vertical
JP3, JP4: POWER; PinHeader_1x02_P2.54mm_Vertical
R5, R8: 10k; R_Axial_DIN0204_L3.6mm_D1.6mm_P5.08mm_Horizontal
R6, R7, R9, R10: 1k; R_Axial_DIN0204_L3.6mm_D1.6mm_P5.08mm_Horizontal
SW2: IP2; SW_PUSH_6mm
SW3: IP3; SW_PUSH_6mm
TP5: IP3; TestPoint_THTPad_2.0x2.0mm_Drill1.0mm
TP6: IP2; TestPoint_THTPad_2.0x2.0mm_Drill1.0mm
U9: MC68681; PLCC-44_THT-Socket
Y2: Crystal; Crystal_HC49-4H_Vertical

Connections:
+5V: JP3.1 (A), JP4.1 (A), R6.2, R7.2, R9.2, R10.2, SW2.2, SW3.2, U9.44 (VCC); also elsewhere on the board
A1: U9.2 (RS1); also elsewhere on the board
A2: U9.4 (RS2); also elsewhere on the board
A3: U9.6 (RS3); also elsewhere on the board
A4: U9.7 (RS4); also elsewhere on the board
D24: U9.28 (D0); also elsewhere on the board
D25: U9.18 (D1); also elsewhere on the board
D26: U9.27 (D2); also elsewhere on the board
D27: U9.19 (D3); also elsewhere on the board
D28: U9.26 (D4); also elsewhere on the board
D29: U9.20 (D5); also elsewhere on the board
D30: U9.25 (D6); also elsewhere on the board
D31: U9.21 (D7); also elsewhere on the board
GND: C4.1, C5.1, J3.6, J4.6, R5.2, R8.2, U9.22 (GND); also elsewhere on the board
IP4: U9.43 (IP4)
IP5: U9.42 (IP5)
unnamed: D2.2 (A), R6.1
unnamed: D2.1 (K), U9.16 (OP5)
unnamed: D3.2 (A), R7.1
unnamed: D3.1 (K), U9.17 (OP7)
unnamed: D4.2 (A), R9.1
unnamed: D4.1 (K), U9.30 (OP4)
unnamed: D5.2 (A), R10.1
unnamed: D5.1 (K), U9.29 (OP6)
unnamed: J3.1, U9.8 (IP0)
unnamed: J3.2, U9.33 (TXDA)
unnamed: J3.3, U9.35 (RXDA)
unnamed: J3.4, JP3.2 (B)
unnamed: J3.5, U9.32 (OP0)
unnamed: J4.1, U9.5 (IP1)
unnamed: J4.2, U9.13 (TXDB)
unnamed: J4.3, U9.11 (RXDB)
unnamed: J4.4, JP4.2 (B)
unnamed: J4.5, U9.14 (OP1)
unnamed: R8.1, SW2.1, TP6.1, U9.40 (IP2)
unnamed: R5.1, SW3.1, TP5.1, U9.3 (IP3)
unnamed: C4.2, U9.36 (X1/CLK), Y2.2
unnamed: C5.2, U9.37 (X2), Y2.1
OP2: U9.31 (OP2)
OP3: U9.15 (OP3)
~DSACK0: U9.10 (DTACK); also elsewhere on the board
~IACK: JP2.1 (A)
~IOSEL: U9.39 (CS)
~IPL1: JP1.1 (A); also elsewhere on the board
~RESET: U9.38 (RESET); also elsewhere on the board
~SIACK: JP2.2 (B), U9.41 (IACK)
~SIRQ: JP1.2 (B), U9.24 (IRQ)
~WR: U9.9 (R/W); also elsewhere on the board
